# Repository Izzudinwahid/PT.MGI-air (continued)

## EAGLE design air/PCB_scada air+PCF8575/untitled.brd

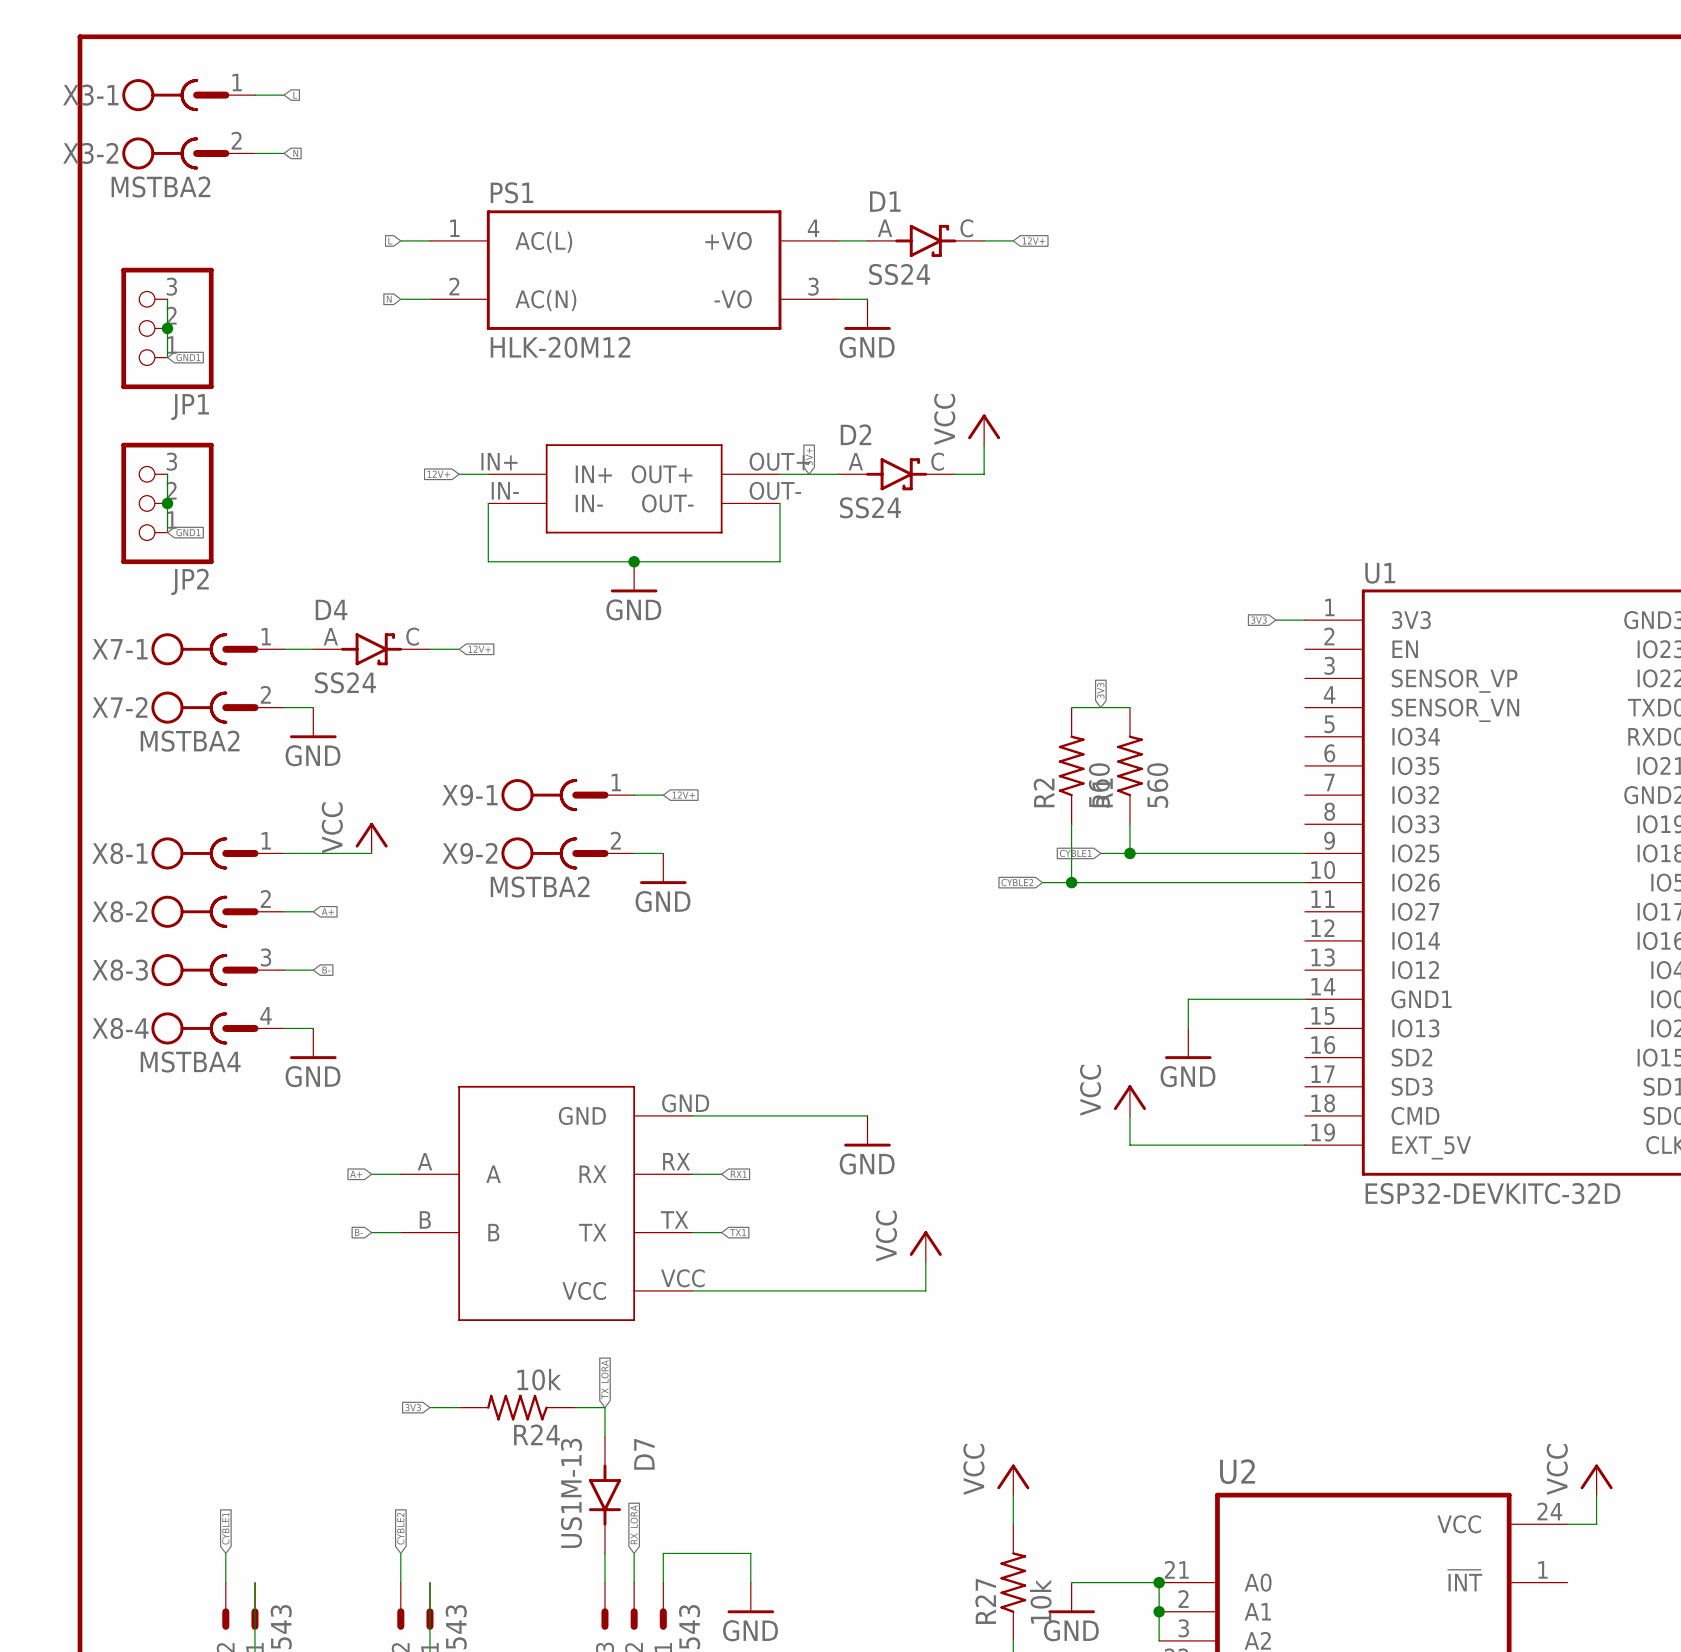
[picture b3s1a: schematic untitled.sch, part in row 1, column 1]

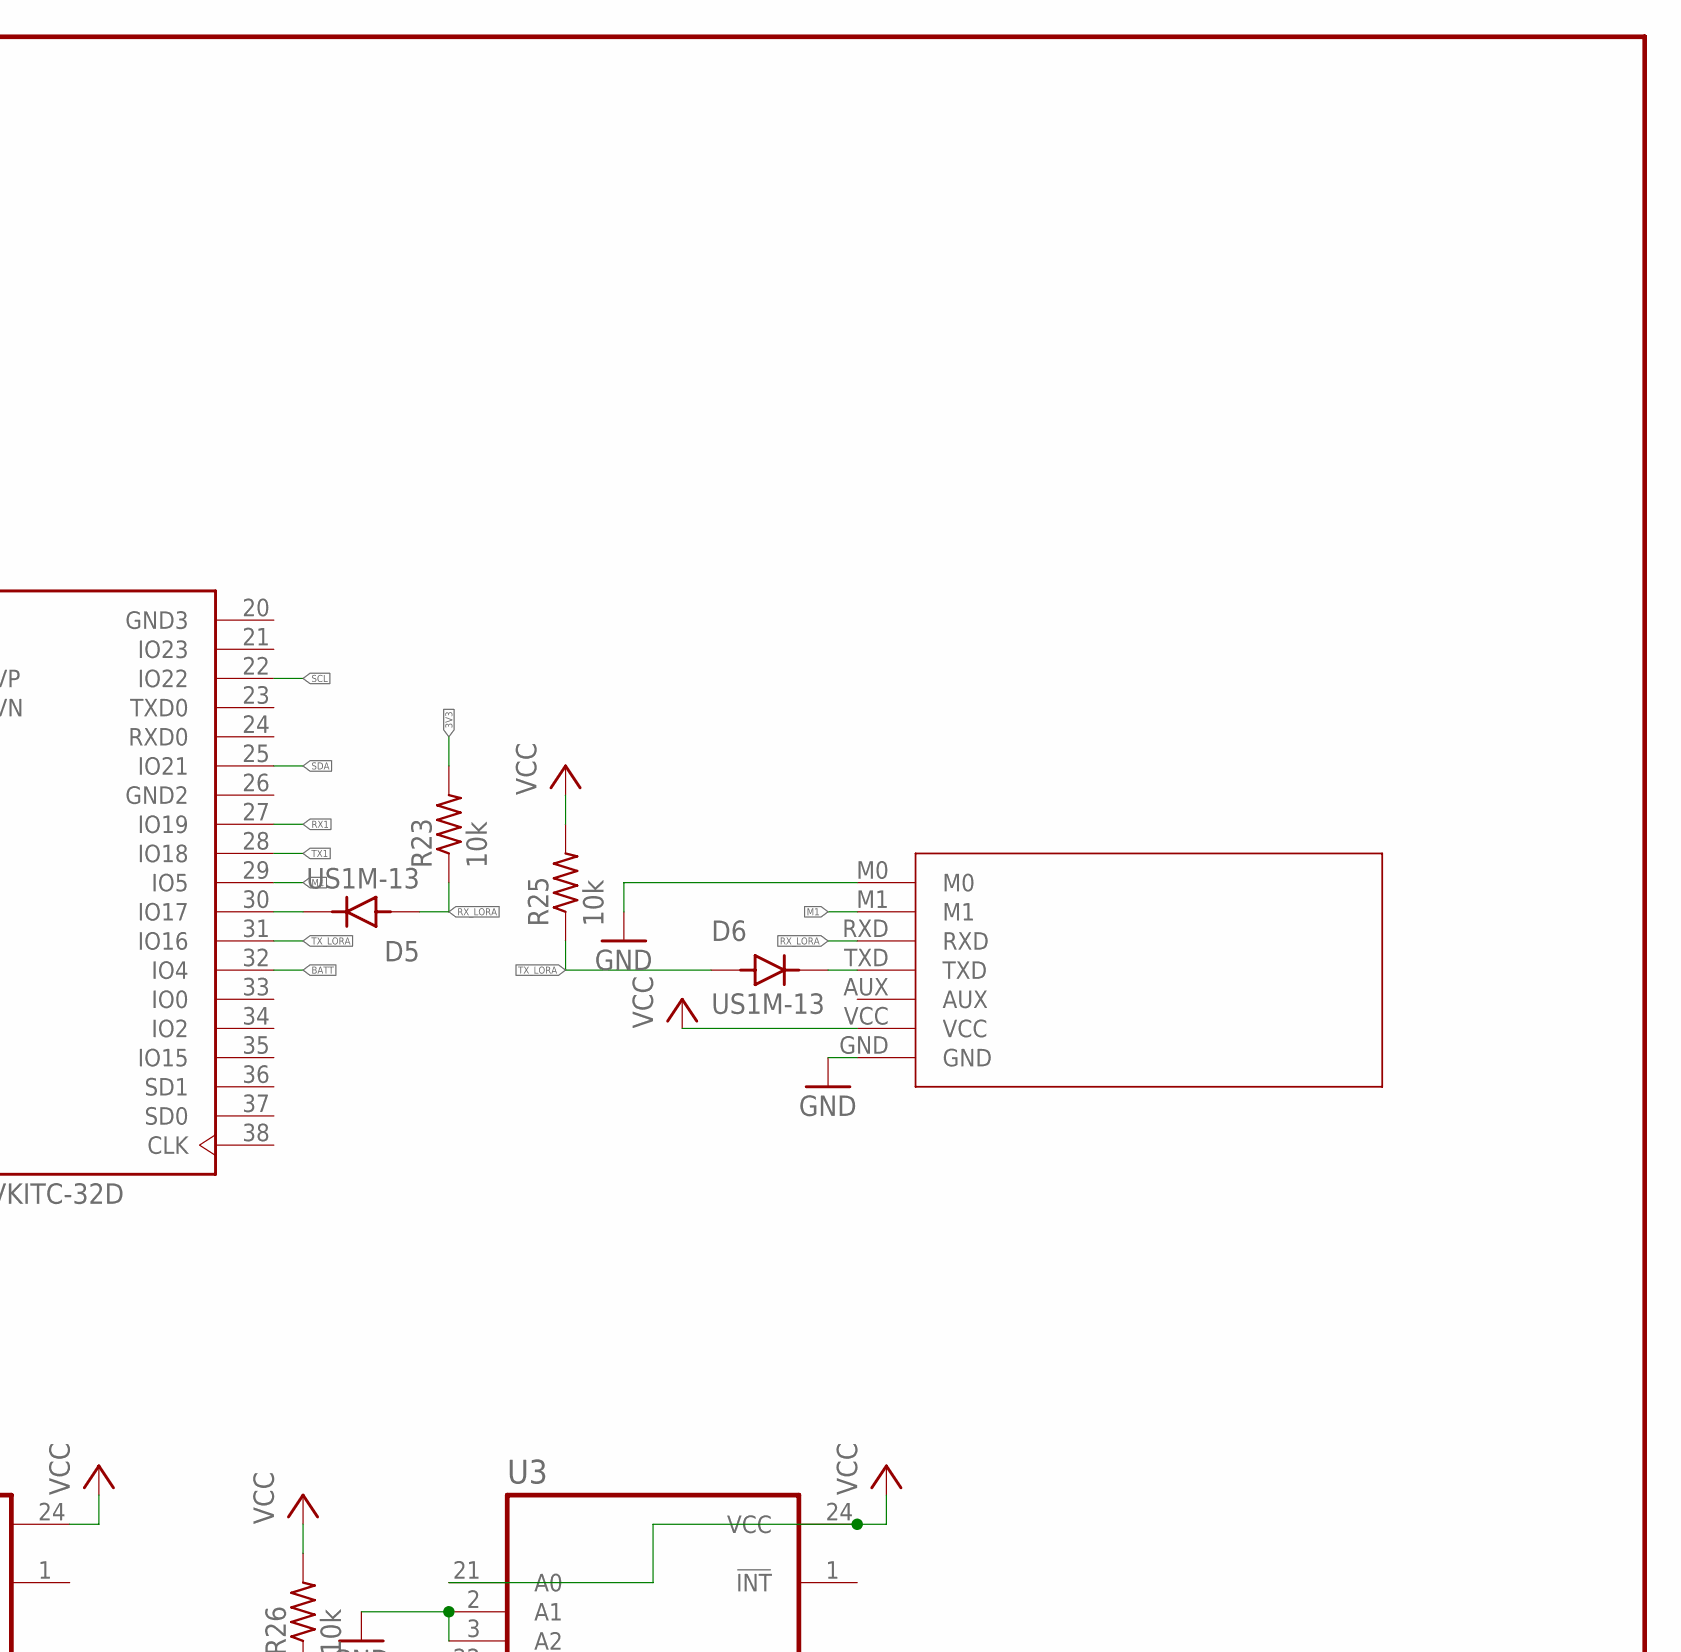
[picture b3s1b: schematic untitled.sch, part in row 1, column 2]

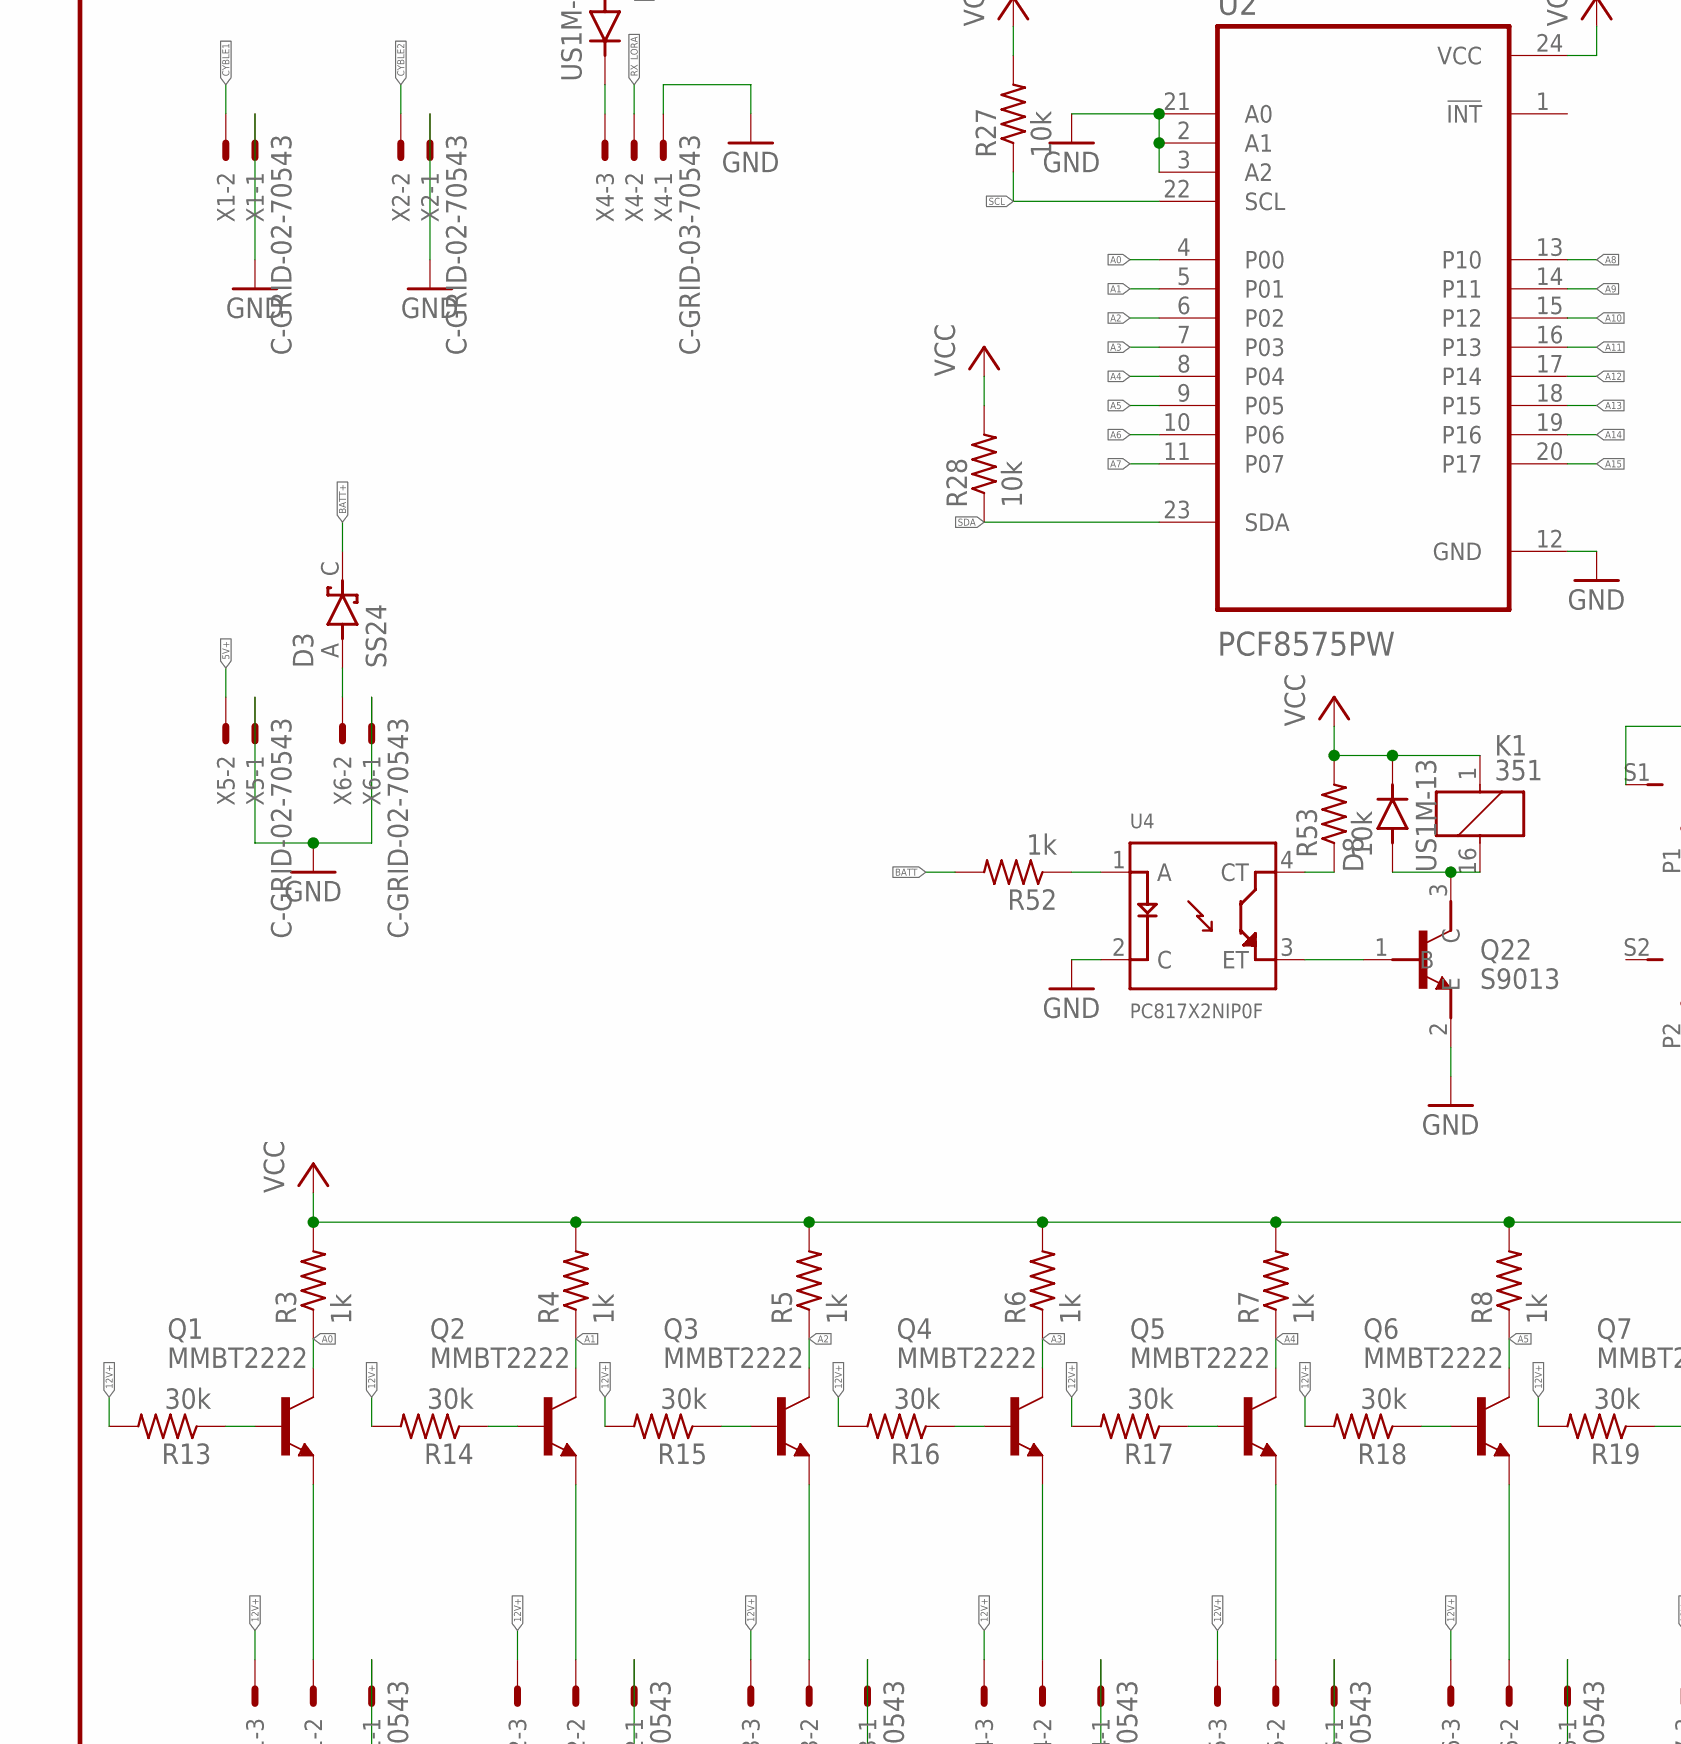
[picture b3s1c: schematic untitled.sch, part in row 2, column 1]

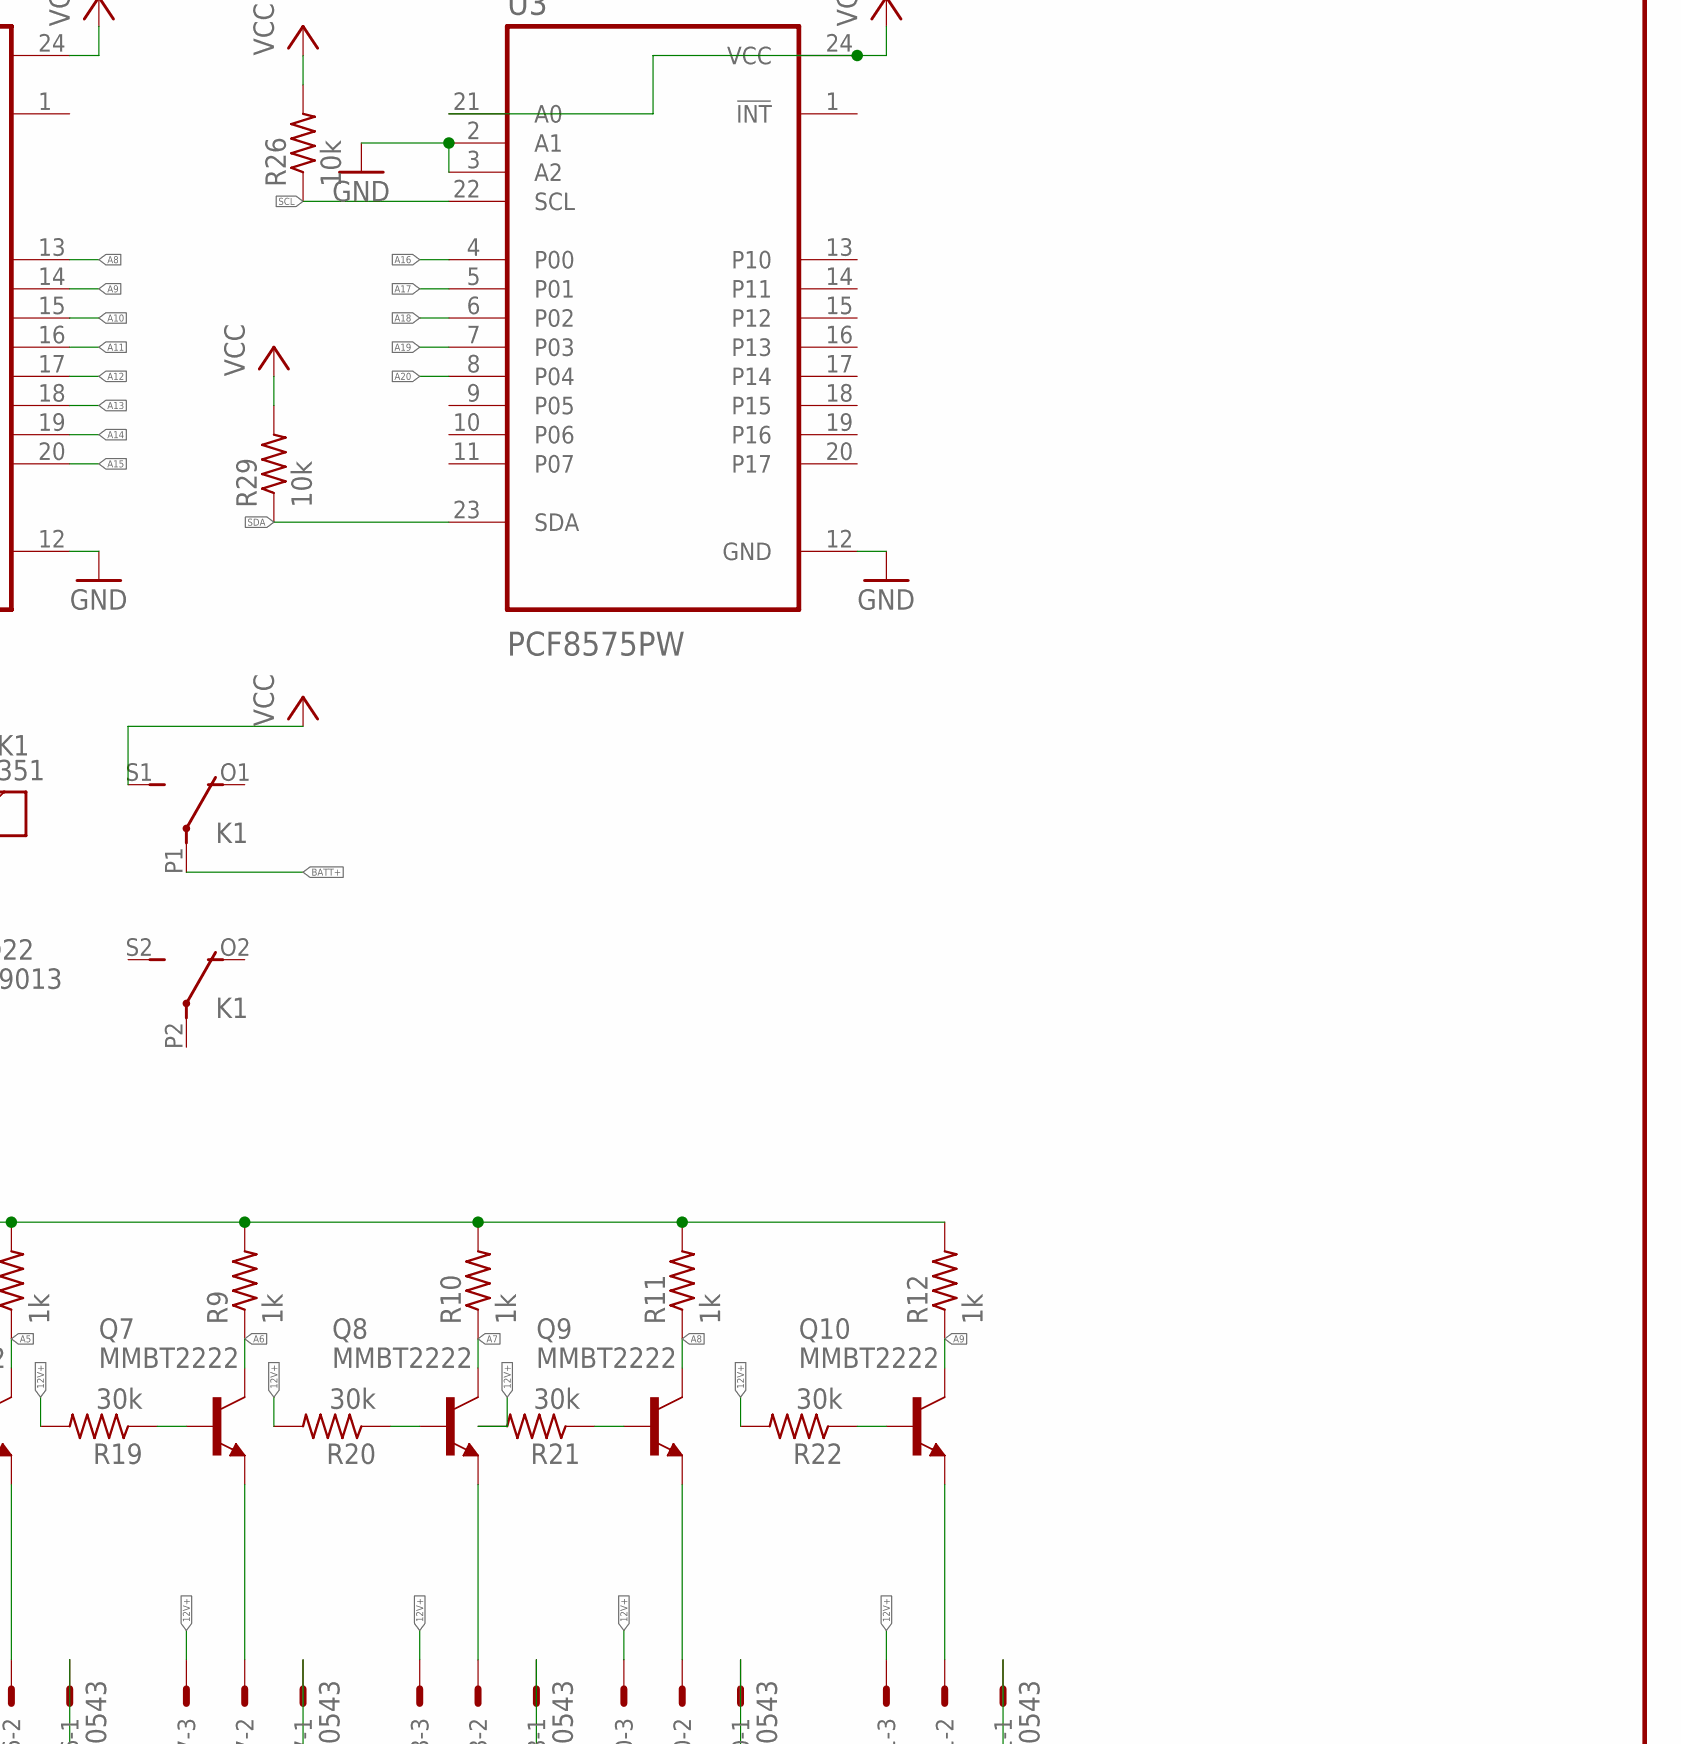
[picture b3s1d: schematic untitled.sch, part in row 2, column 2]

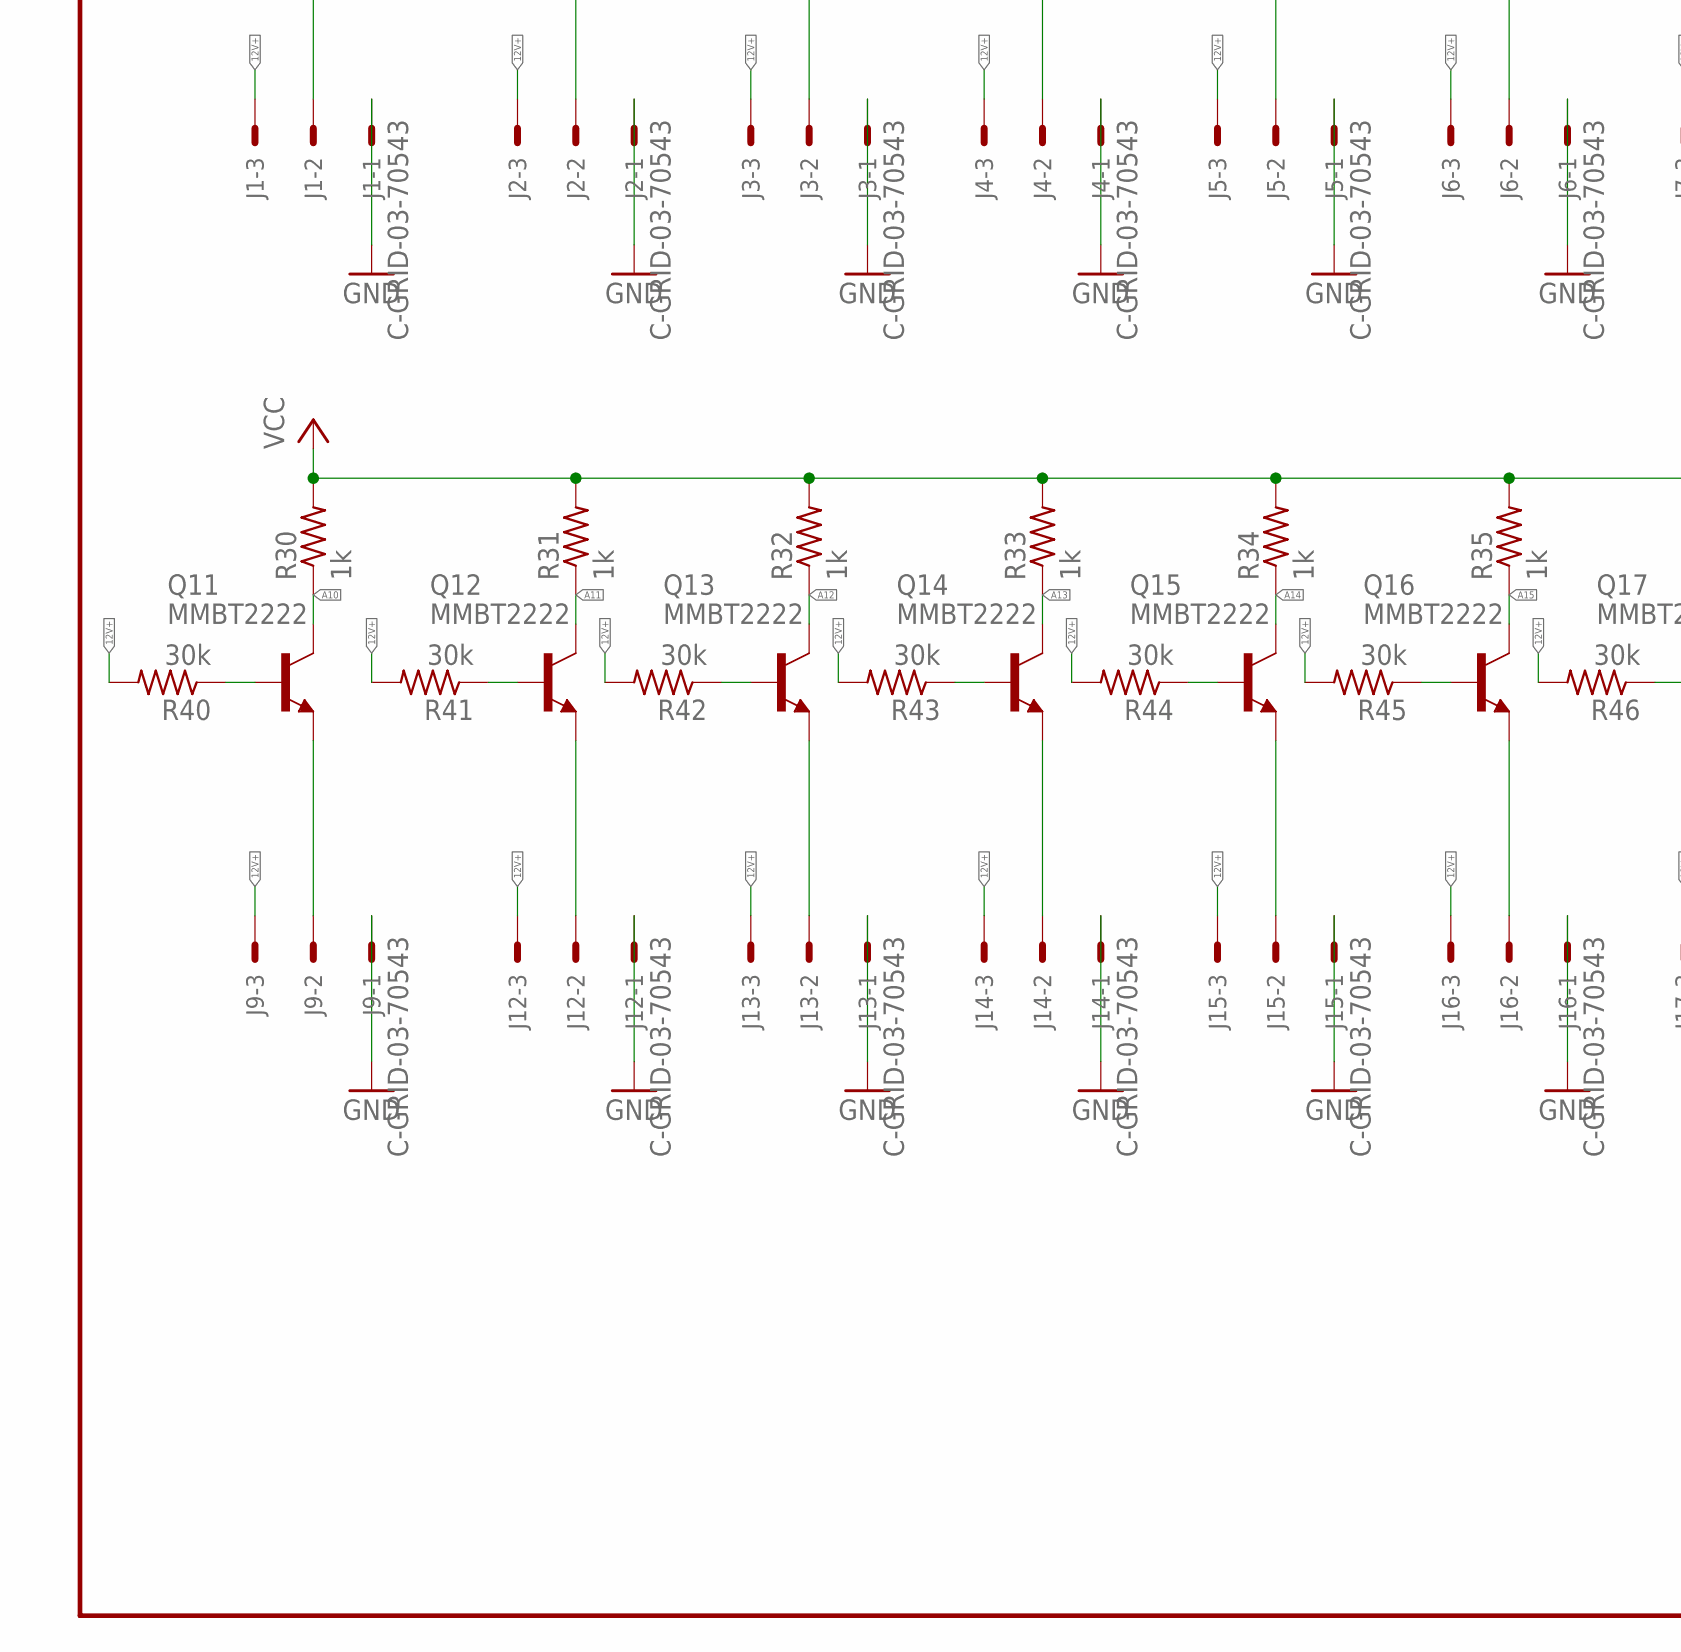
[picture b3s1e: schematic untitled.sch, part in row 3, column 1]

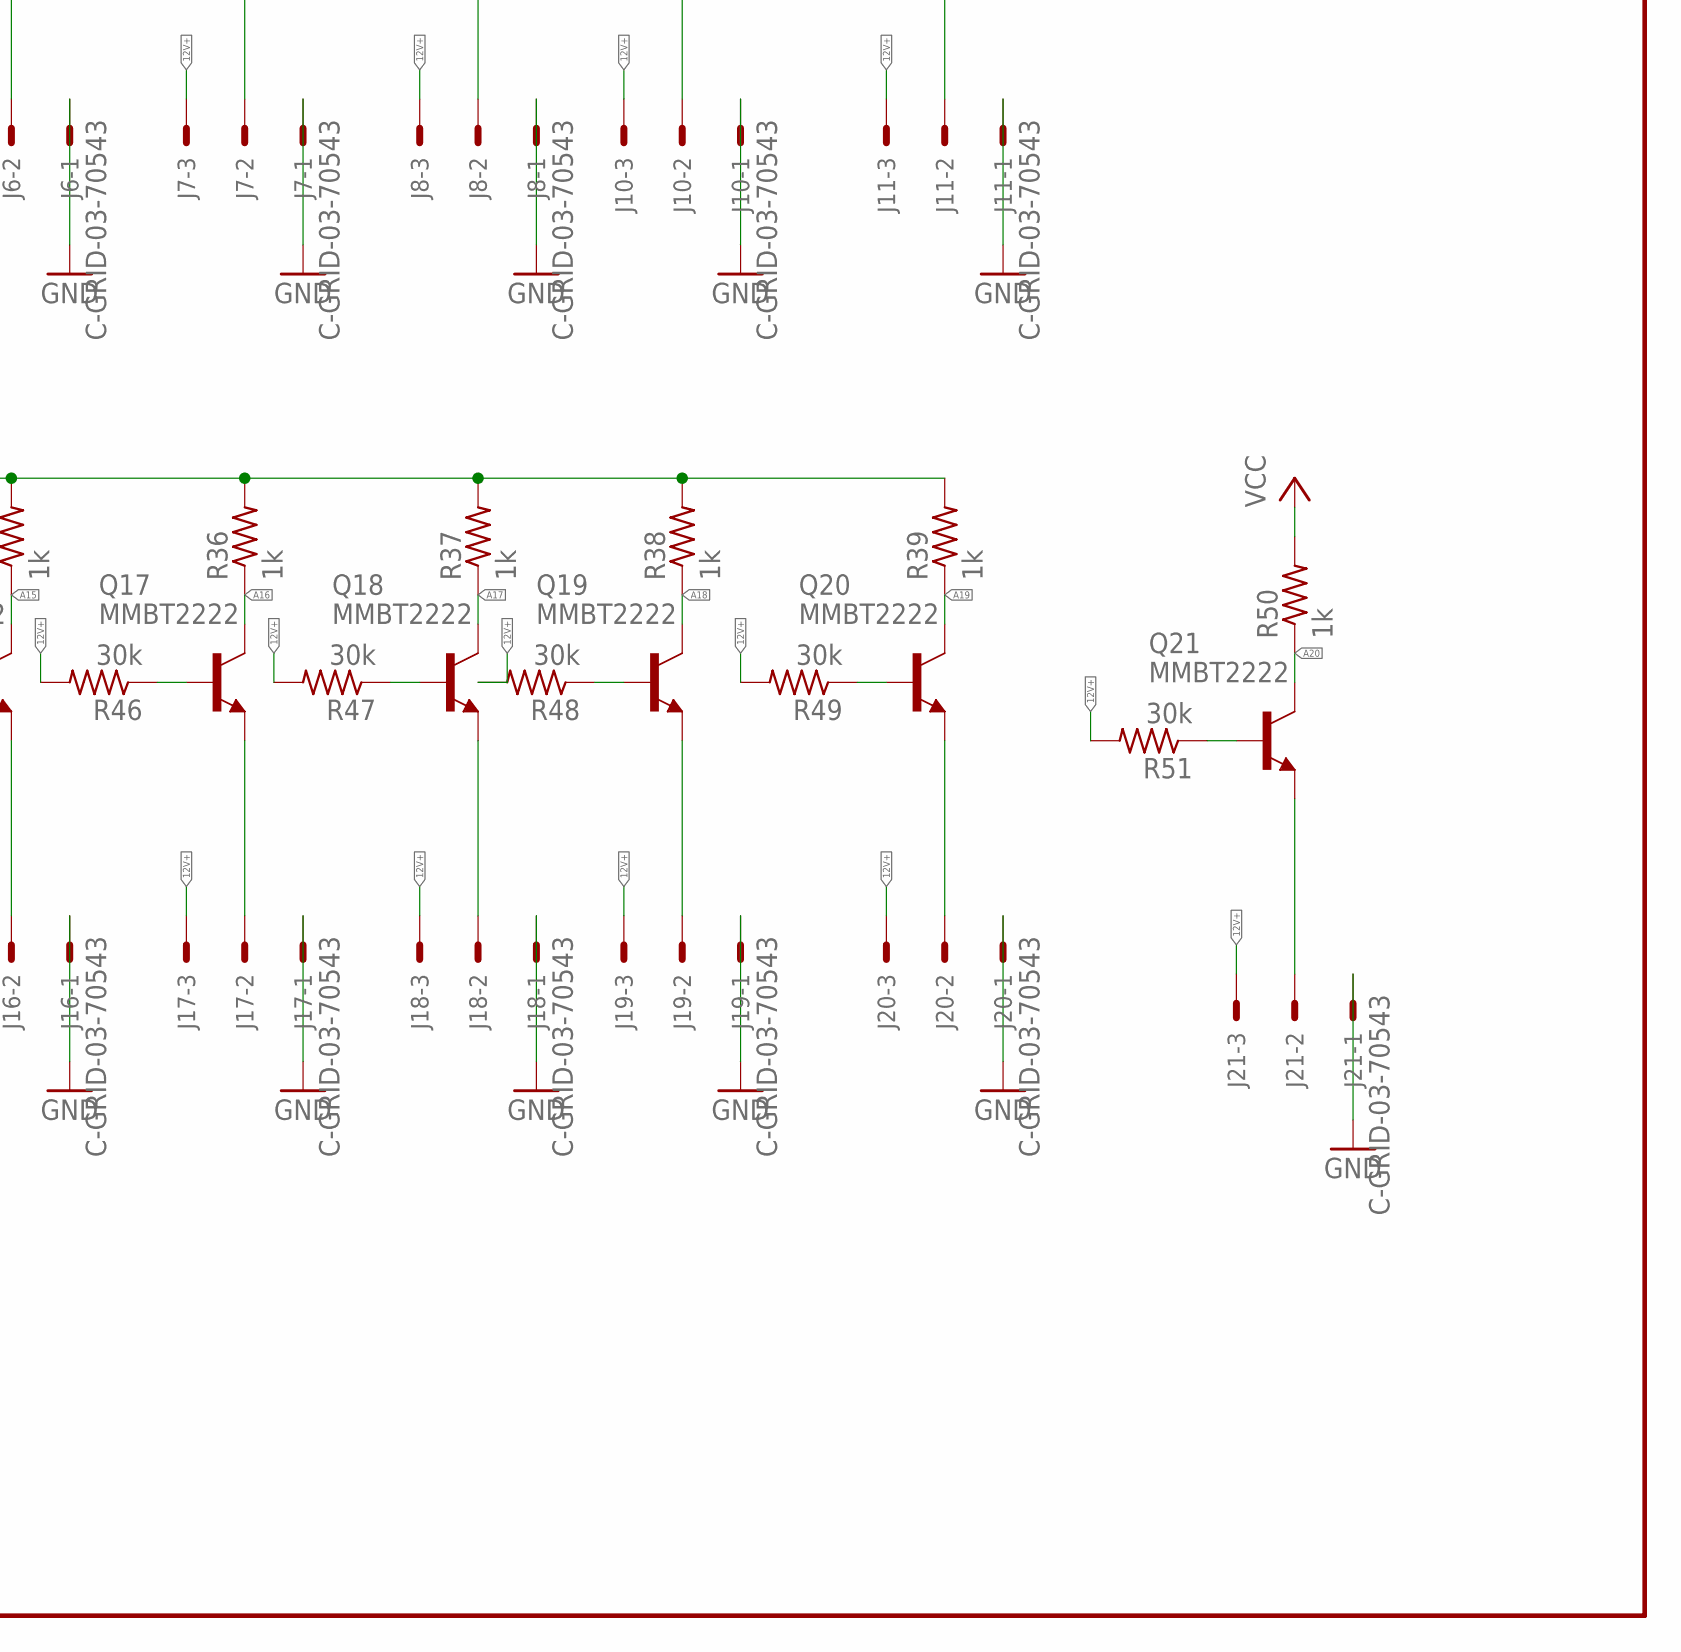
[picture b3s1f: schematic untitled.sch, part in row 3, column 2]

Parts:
D1, D2, D3, D4: SS24; DIOM5336X265N
D5, D6, D7, D8: US1M-13; DIOM5226X240N
EBYTEE220-900T22D1: EBYTEE220-900T22D
J1, J2, J3, J4, J5, J6, J7, J8, J9, J10, J11, J12, J13, J14, J15, J16, J17, J18, J19, J20, J21: C-GRID-03-70543; 70543-03
JP1, JP2: PINHD-1X3CB; 1X03-CLEANBIG
K1: 351
MINI1: MINI560
PS1: HLK-20M12; CONV_HLK-20M12
Q1, Q2, Q3, Q4, Q5, Q6, Q7, Q8, Q9, Q10, Q11, Q12, Q13, Q14, Q15, Q16, Q17, Q18, Q19, Q20, Q21: MMBT2222; SOT23-BEC
Q22: S9013; SOT95P240X120-3N
R1, R2: 560; M0805
R3, R4, R5, R6, R7, R8, R9, R10, R11, R12, R30, R31, R32, R33, R34, R35, R36, R37, R38, R39, R50, R52: 1k; M0805
R13, R14, R15, R16, R17, R18, R19, R20, R21, R22, R40, R41, R42, R43, R44, R45, R46, R47, R48, R49, R51: 30k; M0805
R23, R24, R25, R26, R27, R28, R29, R53: 10k; M0805
TTL-RS1: TTL-RS485
U1: ESP32-DEVKITC-32D; MODULE_ESP32-DEVKITC-32D
U2, U3: PCF8575PW; SOP65P640X120-24N
U4: PC817X2NIP0F; SOT254P975X400-4N
X1, X2, X5, X6: C-GRID-02-70543; 70543-02
X3, X7, X9: MSTBA2
X4: C-GRID-03-70543; 70543-03
X8: MSTBA4

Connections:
3V3: R1.2, R2.2, R23.2, R24.2, U1.1 (3V3)
5V+: D2.A, MINI1.OUT+, X5.2
12V+: D1.C (K), D4.C (K), J1.3, J2.3, J3.3, J4.3, J5.3, J6.3, J7.3, J8.3, J9.3, J10.3, J11.3, J12.3, J13.3, J14.3, J15.3, J16.3, J17.3, J18.3, J19.3, J20.3, J21.3, MINI1.IN+, R13.2, R14.2, R15.2, R16.2, R17.2, R18.2, R19.2, R20.2, R21.2, R22.2, R40.2, R41.2, R42.2, R43.2, R44.2, R45.2, R46.2, R47.2, R48.2, R49.2, R51.2, X9.1
12V++: D1.A, PS1.4 (+VO)
A0: Q1.C, R3.1, U2.4 (P00)
A1: Q2.C, R4.1, U2.5 (P01)
A2: Q3.C, R5.1, U2.6 (P02)
A3: Q4.C, R6.1, U2.7 (P03)
A4: Q5.C, R7.1, U2.8 (P04)
A5: Q6.C, R8.1, U2.9 (P05)
A6: Q7.C, R9.1, U2.10 (P06)
A7: Q8.C, R10.1, U2.11 (P07)
A8: Q9.C, R11.1, U2.13 (P10)
A9: Q10.C, R12.1, U2.14 (P11)
A10: Q11.C, R30.1, U2.15 (P12)
A11: Q12.C, R31.1, U2.16 (P13)
A12: Q13.C, R32.1, U2.17 (P14)
A13: Q14.C, R33.1, U2.18 (P15)
A14: Q15.C, R34.1, U2.19 (P16)
A15: Q16.C, R35.1, U2.20 (P17)
A16: Q17.C, R36.1, U3.4 (P00)
A17: Q18.C, R37.1, U3.5 (P01)
A18: Q19.C, R38.1, U3.6 (P02)
A19: Q20.C, R39.1, U3.7 (P03)
A20: Q21.C, R50.1, U3.8 (P04)
A+: TTL-RS1.A, X8.2
B-: TTL-RS1.B, X8.3
BATT: R52.2, U1.32 (IO4)
BATT+: D3.C (K), K1.P1
CYBLE1: R1.1, U1.9 (IO25), X1.2
CYBLE2: R2.1, U1.10 (IO26), X2.2
GND: EBYTEE220-900T22D1.GND, EBYTEE220-900T22D1.M0, J1.1, J2.1, J3.1, J4.1, J5.1, J6.1, J7.1, J8.1, J9.1, J10.1, J11.1, J12.1, J13.1, J14.1, J15.1, J16.1, J17.1, J18.1, J19.1, J20.1, J21.1, MINI1.IN-, MINI1.OUT-, PS1.3 (-VO), Q22.2 (E), TTL-RS1.GND, U1.14 (GND1), U2.2 (A1), U2.3 (A2), U2.12 (GND), U2.21 (A0), U3.2 (A1), U3.3 (A2), U3.12 (GND), U4.2 (C), X1.1, X2.1, X4.1, X5.1, X6.1, X7.2, X8.4, X9.2
GND1: JP1.1, JP1.2, JP1.3, JP2.1, JP2.2, JP2.3
GND2: U1.26 (GND2)
GND3: U1.20 (GND3)
L: PS1.1 (AC(L)), X3.1
M1: EBYTEE220-900T22D1.M1, U1.29 (IO5)
N: PS1.2 (AC(N)), X3.2
unnamed: Q1.B, R13.1
unnamed: Q2.B, R14.1
unnamed: D3.A, X6.2
unnamed: Q3.B, R15.1
unnamed: Q4.B, R16.1
unnamed: Q5.B, R17.1
unnamed: Q6.B, R18.1
unnamed: Q7.B, R19.1
unnamed: Q8.B, R20.1
unnamed: Q9.B, R21.1
unnamed: Q10.B, R22.1
unnamed: J1.2, Q1.E
unnamed: J2.2, Q2.E
unnamed: J3.2, Q3.E
unnamed: J4.2, Q4.E
unnamed: J5.2, Q5.E
unnamed: J6.2, Q6.E
unnamed: J7.2, Q7.E
unnamed: J8.2, Q8.E
unnamed: J10.2, Q9.E
unnamed: J11.2, Q10.E
unnamed: D4.A, X7.1
unnamed: D6.C (K), EBYTEE220-900T22D1.TXD
unnamed: D5.C (K), U1.30 (IO17)
unnamed: D7.C (K), X4.3
unnamed: Q11.B, R40.1
unnamed: Q12.B, R41.1
unnamed: Q13.B, R42.1
unnamed: Q14.B, R43.1
unnamed: Q15.B, R44.1
unnamed: Q16.B, R45.1
unnamed: Q17.B, R46.1
unnamed: Q18.B, R47.1
unnamed: Q19.B, R48.1
unnamed: Q20.B, R49.1
unnamed: J9.2, Q11.E
unnamed: J12.2, Q12.E
unnamed: J13.2, Q13.E
unnamed: J14.2, Q14.E
unnamed: J15.2, Q15.E
unnamed: J16.2, Q16.E
unnamed: J17.2, Q17.E
unnamed: J18.2, Q18.E
unnamed: J19.2, Q19.E
unnamed: J20.2, Q20.E
unnamed: Q21.B, R51.1
unnamed: J21.2, Q21.E
unnamed: R52.1, U4.1 (A)
unnamed: R53.1, U4.4 (CT)
unnamed: D8.A, K1.16 (2), Q22.3 (C)
unnamed: Q22.1 (B), U4.3 (ET)
RX1: TTL-RS1.RX, U1.27 (IO19)
RX_LORA: D5.A, EBYTEE220-900T22D1.RXD, R23.1, X4.2
SCL: R26.1, R27.1, U1.22 (IO22), U2.22 (SCL), U3.22 (SCL)
SDA: R28.1, R29.1, U1.25 (IO21), U2.23 (SDA), U3.23 (SDA)
TX1: TTL-RS1.TX, U1.28 (IO18)
TX_LORA: D6.A, D7.A, R24.1, R25.1, U1.31 (IO16)
VCC: D2.C (K), D8.C (K), EBYTEE220-900T22D1.VCC, K1.1, K1.S1 (S), R3.2, R4.2, R5.2, R6.2, R7.2, R8.2, R9.2, R10.2, R11.2, R12.2, R25.2, R26.2, R27.2, R28.2, R29.2, R30.2, R31.2, R32.2, R33.2, R34.2, R35.2, R36.2, R37.2, R38.2, R39.2, R50.2, R53.2, TTL-RS1.VCC, U1.19 (EXT_5V), U2.24 (VCC), U3.21 (A0), U3.24 (VCC), X8.1

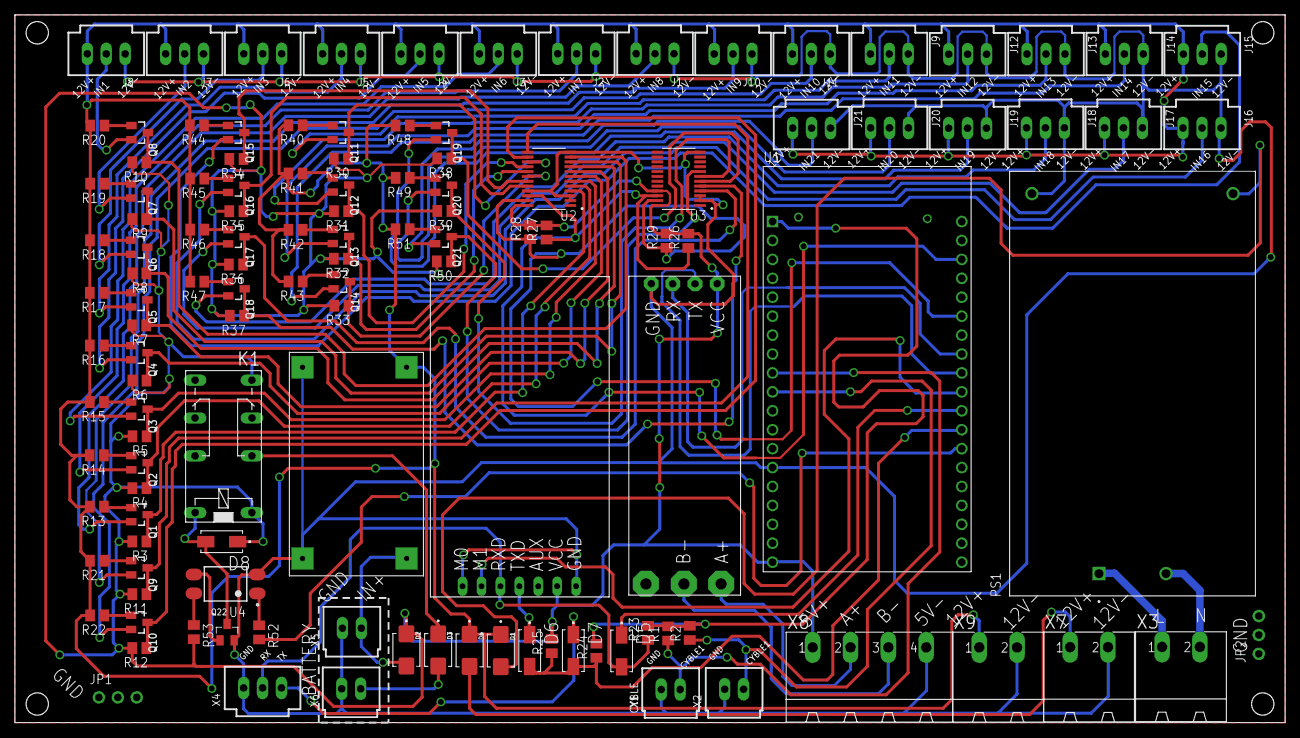
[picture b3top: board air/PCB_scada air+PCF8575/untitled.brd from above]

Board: 2 copper layers, 170.5 x 95.0 mm, 124 parts (0 on the bottom side), 94 nets.
